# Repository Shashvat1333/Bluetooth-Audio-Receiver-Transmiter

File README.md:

# AUX-to-Bluetooth Audio Transmitter

A custom PCB I designed in KiCad that adds Bluetooth to anything with a headphone jack. Plug in an AUX cable, power it over USB-C, and stream to your wireless headphones.

## Table of Contents
- [Overview](#overview)
- [Repository Structure](#repository-structure)
- [Schematic & PCB](#schematic--pcb)
- [Firmware](#firmware)
- [Getting Started](#getting-started)
- [Ordering the Board](#ordering-the-board)
- [Bill of Materials (BOM)](#bill-of-materials-bom)
- [License](#license)

## Overview

Lots of good gear has no Bluetooth: an old TV, a record player, a treadmill, a car stereo with an AUX port. I wanted one small board that fixes that, so I designed it myself, from the schematic to the PCB layout.

### What it does

- **Wired to wireless:** Takes analog audio from a standard 3.5 mm AUX cable.
- **Clean conversion:** A 24-bit stereo ADC turns the sound into digital audio.
- **Bluetooth streaming:** An ESP32 sends the audio to your headphones or speaker.
- **Long range:** An RP-SMA connector lets you attach an external antenna.

### Real-world examples

- **Old TV:** Watch late at night with AirPods, no cable across the room.
- **Record player:** Listen to vinyl on wireless headphones.
- **Gym treadmill:** No cable in your way while you run.

---

## Repository Structure

```
Bluetooth-Audio-Receiver-Transmiter/
├── Hardware/    # KiCad project (schematic + PCB)
├── Gerbers/     # Files for the PCB factory
├── BOM/         # Full parts list
├── Firmware/    # ESP32 code
├── LICENSE.md
└── README.md
```

---

## Schematic & PCB

Audio goes in through the AUX jack, gets digitized, and is sent out over Bluetooth:

```
AUX jack → PCM1808 (ADC) → ESP32 (Bluetooth) → your headphones
```

| Part | What it does |
|---|---|
| ESP32-WROOM-32UE-N4 | The brain: Bluetooth pairing and streaming |
| PCM1808PWR | Turns analog sound into digital (I2S) audio |
| AP2112K-3.3 | Steps USB 5 V down to a steady 3.3 V |
| CH340C | USB-to-serial chip so you can upload code over USB-C |
| SJ-3523-SMT-TR | 3.5 mm stereo input jack |

---

## Firmware

The ESP32 needs code before the board will do anything. You upload it once with the Arduino IDE.

- **Code:** [firmware.ino](https://github.com/Shashvat1333/Bluetooth-Audio-Transmiter/blob/main/firmware.ino)
- **Board:** ESP32 Dev Module
- **Port:** USB-C (this one port both powers the board **and** uploads the code)

---

## Getting Started

1. **Download the firmware:** Grab the code from the [firmware.ino](https://github.com/Shashvat1333/Bluetooth-Audio-Transmiter/blob/main/firmware.ino).
2. **Set up the Arduino IDE:** Install the ESP32 board package (Boards Manager → search "esp32").
3. **Connect the board:** Plug the board into your computer with a USB-C cable. This one cable powers the board **and** uploads the code.
4. **Select the board:** Tools → Board → **ESP32 Dev Module**, then pick the correct port under Tools → Port.
5. **Upload:** Open the firmware file and click **Upload**.
6. **Plug in your audio:** Connect your audio source to the 3.5 mm AUX jack.
7. **Pair:** Put your headphones in pairing mode. The board connects automatically.

> **Tip:** If your computer doesn't show a port, install the CH340 USB driver and try a different USB-C cable (some are charge-only).

After the first upload, you only need USB-C power. Any phone charger works.

---

## Ordering the Board

Zip the `Gerbers` folder and upload it to your PCB maker (JLCPCB, PCBWay, etc.) with these settings:

| Setting | Value |
|---|---|
| Layers | [2] |
| Board size | [110 x 30 mm] |
| Thickness | [1.6 mm] |
| Copper | [1 oz] |
| Surface finish | [HASL lead-free] |
| Solder mask | [Green] |

---

## Bill of Materials (BOM)

| Part | What it's for | Qty | Unit | Total | Vendor |
| --- | --- | --- | --- | --- | --- |
| [UJ20-C-H-G-SMT-1-P16-TR](https://jlcpcb.com/partdetail/CUI-UJ20_C_H_G_SMT_1_P16TR/C45082766) | Use to power and program the esp32 | 1 | $0.86 | $0.86 | [JLCPCB](https://jlcpcb.com/partdetail/CUI-UJ20_C_H_G_SMT_1_P16TR/C45082766) |
| [Ceramic Capacitor Assortment Kit](https://www.aliexpress.com/item/1005012290380278.html?spm=a2g0o.productlist.main.2.328544d8SuTRhb&algo_pvid=40487480-af34-4fa0-991f-8491ed68449b&algo_exp_id=40487480-af34-4fa0-991f-8491ed68449b-1&pdp_ext_f=%7B%22order%22%3A%22786%22%2C%22eval%22%3A%221%22%2C%22fromPage%22%3A%22search%22%7D&pdp_npi=6%40dis%21CAD%2111.33%219.88%21%21%2152.17%2145.49%21%402103128817917564117867231e1157%2112000057969079635%21sea%21CA%218048449113%21X%211%210%21n_tag%3A-29911%3Bd%3A979b4513%3Bm03_new_user%3A-29895%3BpisId%3A5000000218598348&curPageLogUid=g6HIOIDwDsUK&utparam-url=scene%3Asearch%7Cquery_from%3A%7Cx_object_id%3A1005012290380278%7C_p_origin_prod%3A) | Ceramic capacitors are tiny passive electronic components used here to filter out electrical noise on power rails and block DC voltage while letting audio signals pass through. | 1 | $13.64 | $13.64 | [Aliexpress](https://www.aliexpress.com/item/1005012290380278.html?spm=a2g0o.productlist.main.2.328544d8SuTRhb&algo_pvid=40487480-af34-4fa0-991f-8491ed68449b&algo_exp_id=40487480-af34-4fa0-991f-8491ed68449b-1&pdp_ext_f=%7B%22order%22%3A%22786%22%2C%22eval%22%3A%221%22%2C%22fromPage%22%3A%22search%22%7D&pdp_npi=6%40dis%21CAD%2111.33%219.88%21%21%2152.17%2145.49%21%402103128817917564117867231e1157%2112000057969079635%21sea%21CA%218048449113%21X%211%210%21n_tag%3A-29911%3Bd%3A979b4513%3Bm03_new_user%3A-29895%3BpisId%3A5000000218598348&curPageLogUid=g6HIOIDwDsUK&utparam-url=scene%3Asearch%7Cquery_from%3A%7Cx_object_id%3A1005012290380278%7C_p_origin_prod%3A) |
| [AP2112K-3.3TRG1](https://jlcpcb.com/partdetail/DiodesIncorporated-AP2112K_33TRG1/C51118) | The AP2112K-3.3TRG1 is a low-dropout (LDO) voltage regulator used here to step down your incoming 5V power supply to a steady, clean 3.3V to power the ESP32 microcontroller and digital logic pins. | 1 | $0.19 | $0.19 | [JLCPCB](https://jlcpcb.com/partdetail/DiodesIncorporated-AP2112K_33TRG1/C51118) |
| [ESP32-WROOM-32UE-N4](https://jlcpcb.com/partdetail/EspressifSystems-ESP32_WROOM_32UEN4/C701344) | The ESP32 is a microcontroller used here to run firmware that receives the digital I2S audio stream from the PCM1808 and handles Wi-Fi or Bluetooth connectivity. | 1 | $4.50 | $4.50 | [JLCPCB](https://jlcpcb.com/partdetail/EspressifSystems-ESP32_WROOM_32UEN4/C701344) |
| [CH340C](https://www.aliexpress.com/item/1005007206307679.html?spm=a2g0o.productlist.main.2.14735d38jJiEP4&algo_pvid=08c2775b-a139-455d-8b44-be4d4204f0a8&algo_exp_id=08c2775b-a139-455d-8b44-be4d4204f0a8-1&pdp_ext_f=%7B%22order%22%3A%2220%22%2C%22eval%22%3A%221%22%2C%22fromPage%22%3A%22search%22%7D&pdp_npi=6%40dis%21CAD%214.39%214.39%21%21%213.02%213.02%21%402101c28d17917628228577887e0c6e%2112000039805627300%21sea%21CA%218048449113%21X%211%210%21n_tag%3A-29911%3Bd%3A979b4513%3Bm03_new_user%3A-29895&curPageLogUid=tDRd9NJte0Jp&utparam-url=scene%3Asearch%7Cquery_from%3A%7Cx_object_id%3A1005007206307679%7C_p_origin_prod%3A) | The CH340C is a USB-to-UART bridge IC used here to let your computer communicate with the ESP32 for programming and debugging via a standard USB-C cable. | 1 | $4.20 | $4.20 | [Aliexpress](https://www.aliexpress.com/item/1005007206307679.html?spm=a2g0o.productlist.main.2.14735d38jJiEP4&algo_pvid=08c2775b-a139-455d-8b44-be4d4204f0a8&algo_exp_id=08c2775b-a139-455d-8b44-be4d4204f0a8-1&pdp_ext_f=%7B%22order%22%3A%2220%22%2C%22eval%22%3A%221%22%2C%22fromPage%22%3A%22search%22%7D&pdp_npi=6%40dis%21CAD%214.39%214.39%21%21%213.02%213.02%21%402101c28d17917628228577887e0c6e%2112000039805627300%21sea%21CA%218048449113%21X%211%210%21n_tag%3A-29911%3Bd%3A979b4513%3Bm03_new_user%3A-29895&curPageLogUid=tDRd9NJte0Jp&utparam-url=scene%3Asearch%7Cquery_from%3A%7Cx_object_id%3A1005007206307679%7C_p_origin_prod%3A) |
| [[NC]2.4GHz 3dBi WiFi 2.4g Antenna +15cm Aerial RP-SMA Male Wireless Router PCI U.FL IPX To RP SMA Male Pigtail Cable[NC]](https://www.aliexpress.com/item/1005012839987115.html?spm=a2g0o.productlist.main.17.22487e4aAc5l2Y&algo_pvid=5c910e90-451d-4eb2-b6c2-a9b67833a777&algo_exp_id=5c910e90-451d-4eb2-b6c2-a9b67833a777-16&pdp_ext_f=%7B%22order%22%3A%228%22%2C%22eval%22%3A%221%22%2C%22fromPage%22%3A%22search%22%7D&pdp_npi=6%40dis%21CAD%2112.90%215.00%21%21%2159.41%2123.03%21%402101e80b17915677645397405e0de8%2112000059523438374%21sea%21CA%218048449113%21X%211%210%21n_tag%3A-29911%3Bd%3A979b4513%3Bm03_new_user%3A-29895%3BpisId%3A5000000216666461&curPageLogUid=c4JAZG0wstCM&utparam-url=scene%3Asearch%7Cquery_from%3A%7Cx_object_id%3A1005012839987115%7C_p_origin_prod%3A) | That antenna and pigtail cable are used here to connect an external 2.4GHz antenna to the ESP32 module's IPEX connector for reliable Wi-Fi and Bluetooth signal reception. | 1 | $10.23 | $10.23 | [Aliexpress](https://www.aliexpress.com/item/1005012839987115.html?spm=a2g0o.productlist.main.17.22487e4aAc5l2Y&algo_pvid=5c910e90-451d-4eb2-b6c2-a9b67833a777&algo_exp_id=5c910e90-451d-4eb2-b6c2-a9b67833a777-16&pdp_ext_f=%7B%22order%22%3A%228%22%2C%22eval%22%3A%221%22%2C%22fromPage%22%3A%22search%22%7D&pdp_npi=6%40dis%21CAD%2112.90%215.00%21%21%2159.41%2123.03%21%402101e80b17915677645397405e0de8%2112000059523438374%21sea%21CA%218048449113%21X%211%210%21n_tag%3A-29911%3Bd%3A979b4513%3Bm03_new_user%3A-29895%3BpisId%3A5000000216666461&curPageLogUid=c4JAZG0wstCM&utparam-url=scene%3Asearch%7Cquery_from%3A%7Cx_object_id%3A1005012839987115%7C_p_origin_prod%3A) |
| [Mini Optical Audio Adapter 3.5mm Female Jack to Digital Toslink Male Plug For Amplifier Optical Audio Cable](https://www.aliexpress.com/item/1005009093776595.html?spm=a2g0o.productlist.main.6.18e47348zV59Cg&algo_pvid=f7d36bc0-4bf3-4565-acc6-9d3dda11366b&algo_exp_id=f7d36bc0-4bf3-4565-acc6-9d3dda11366b-5&pdp_ext_f=%7B%22order%22%3A%22344%22%2C%22eval%22%3A%221%22%2C%22fromPage%22%3A%22search%22%7D&pdp_npi=6%40dis%21CAD%213.75%213.75%21%21%2117.28%2117.28%21%402101de2517917626141065991e144b%2112000047887714520%21sea%21CA%218048449113%21X%211%210%21n_tag%3A-29911%3Bd%3A979b4513%3Bm03_new_user%3A-29895&curPageLogUid=tx4CSSuvm17a&utparam-url=scene%3Asearch%7Cquery_from%3A%7Cx_object_id%3A1005009093776595%7C_p_origin_prod%3A) | That adapter is used to convert a standard 3.5mm audio cable connection into a digital optical Toslink plug. | 1 | $2.97 | $2.97 | [Aliexpress](https://www.aliexpress.com/item/1005009093776595.html?spm=a2g0o.productlist.main.6.18e47348zV59Cg&algo_pvid=f7d36bc0-4bf3-4565-acc6-9d3dda11366b&algo_exp_id=f7d36bc0-4bf3-4565-acc6-9d3dda11366b-5&pdp_ext_f=%7B%22order%22%3A%22344%22%2C%22eval%22%3A%221%22%2C%22fromPage%22%3A%22search%22%7D&pdp_npi=6%40dis%21CAD%213.75%213.75%21%21%2117.28%2117.28%21%402101de2517917626141065991e144b%2112000047887714520%21sea%21CA%218048449113%21X%211%210%21n_tag%3A-29911%3Bd%3A979b4513%3Bm03_new_user%3A-29895&curPageLogUid=tx4CSSuvm17a&utparam-url=scene%3Asearch%7Cquery_from%3A%7Cx_object_id%3A1005009093776595%7C_p_origin_prod%3A) |
| [SJ-3523-SMT-TR](https://jlcpcb.com/partdetail/CUI-SJ_3523_SMTTR/C4991872) | The SJ-3523-SMT-TR is a surface-mount 3.5mm stereo audio jack used here to plug in your audio cable and bring the analog sound signals onto the PCB. | 1 | $1.42 | $1.42 | [JLCPCB](https://jlcpcb.com/partdetail/CUI-SJ_3523_SMTTR/C4991872) |
| [PCM1808PWR](https://jlcpcb.com/partdetail/TexasInstruments-PCM1808PWR/C55513) | The PCM1808PWR is a 24-bit stereo analog-to-digital converter (ADC) used here to convert your analog audio signals into digital I2S data for the ESP32. | 1 | $0.79 | $0.79 | [JLCPCB](https://jlcpcb.com/partdetail/TexasInstruments-PCM1808PWR/C55513) |
| [BC817](https://jlcpcb.com/partdetail/2494-BC817_RANGE_100_250/C2137) | The BC817 is a general-purpose NPN transistor used here to act as a switch—typically for driving indicator LEDs, controlling power lines, or handling USB reset signals in your circuit. | 2 | $0.07 | $0.14 | [JLCPCB](https://jlcpcb.com/partdetail/2494-BC817_RANGE_100_250/C2137) |
| [Resistor Kit](https://www.aliexpress.com/item/1005011772534173.html?spm=a2g0o.productlist.main.1.32f07cfcDAKt5h&algo_pvid=bd1a798f-1e1b-462e-8c2c-269d4ca4ad23&algo_exp_id=bd1a798f-1e1b-462e-8c2c-269d4ca4ad23-0&pdp_ext_f=%7B%22order%22%3A%229084%22%2C%22spu_best_type%22%3A%22price%22%2C%22eval%22%3A%221%22%2C%22fromPage%22%3A%22search%22%7D&pdp_npi=6%40dis%21CAD%216.03%214.58%21%21%2127.77%2121.09%21%402101e7a317917668551207826e0eb3%2112000056500803485%21sea%21CA%218048449113%21X%211%210%21n_tag%3A-29911%3Bd%3A979b4513%3Bm03_new_user%3A-29895%3BpisId%3A5000000218598348&curPageLogUid=XejYrzptMOfz&utparam-url=scene%3Asearch%7Cquery_from%3A%7Cx_object_id%3A1005011772534173%7C_p_origin_prod%3A) | A resistor kit is a collection of various resistors with different resistance values used across your circuit for setting up pull-up/pull-down lines, limiting current to LEDs, and biasing transistors. | 1 | $4.78 | $4.78 | [Aliexpress](https://www.aliexpress.com/item/1005011772534173.html?spm=a2g0o.productlist.main.1.32f07cfcDAKt5h&algo_pvid=bd1a798f-1e1b-462e-8c2c-269d4ca4ad23&algo_exp_id=bd1a798f-1e1b-462e-8c2c-269d4ca4ad23-0&pdp_ext_f=%7B%22order%22%3A%229084%22%2C%22spu_best_type%22%3A%22price%22%2C%22eval%22%3A%221%22%2C%22fromPage%22%3A%22search%22%7D&pdp_npi=6%40dis%21CAD%216.03%214.58%21%21%2127.77%2121.09%21%402101e7a317917668551207826e0eb3%2112000056500803485%21sea%21CA%218048449113%21X%211%210%21n_tag%3A-29911%3Bd%3A979b4513%3Bm03_new_user%3A-29895%3BpisId%3A5000000218598348&curPageLogUid=XejYrzptMOfz&utparam-url=scene%3Asearch%7Cquery_from%3A%7Cx_object_id%3A1005011772534173%7C_p_origin_prod%3A) |
| [PCB Manufacturing](https://cart.jlcpcb.com/quote?stencilLayer=2&stencilWidth=100&stencilLength=100&stencilCounts=5&plateType=1&spm=Jlcpcb.Homepage.1010) | This will be the board where I will connect all my parts too | 1 | $8.53 | $8.53 | [JLCPCB](https://cart.jlcpcb.com/quote?stencilLayer=2&stencilWidth=100&stencilLength=100&stencilCounts=5&plateType=1&spm=Jlcpcb.Homepage.1010) |
| **Parts subtotal** | — | — | — | **$52.25** | — |
| **Tax & shipping** | — | — | — | **$12.00** | — |
| **Total** | — | — | — | **$64.25** | — |

---

## License

[License, e.g. CERN-OHL-P or MIT]. See [LICENSE.md](https://github.com/Shashvat1333/Bluetooth-Audio-Transmiter/blob/main/LICENCE.md).

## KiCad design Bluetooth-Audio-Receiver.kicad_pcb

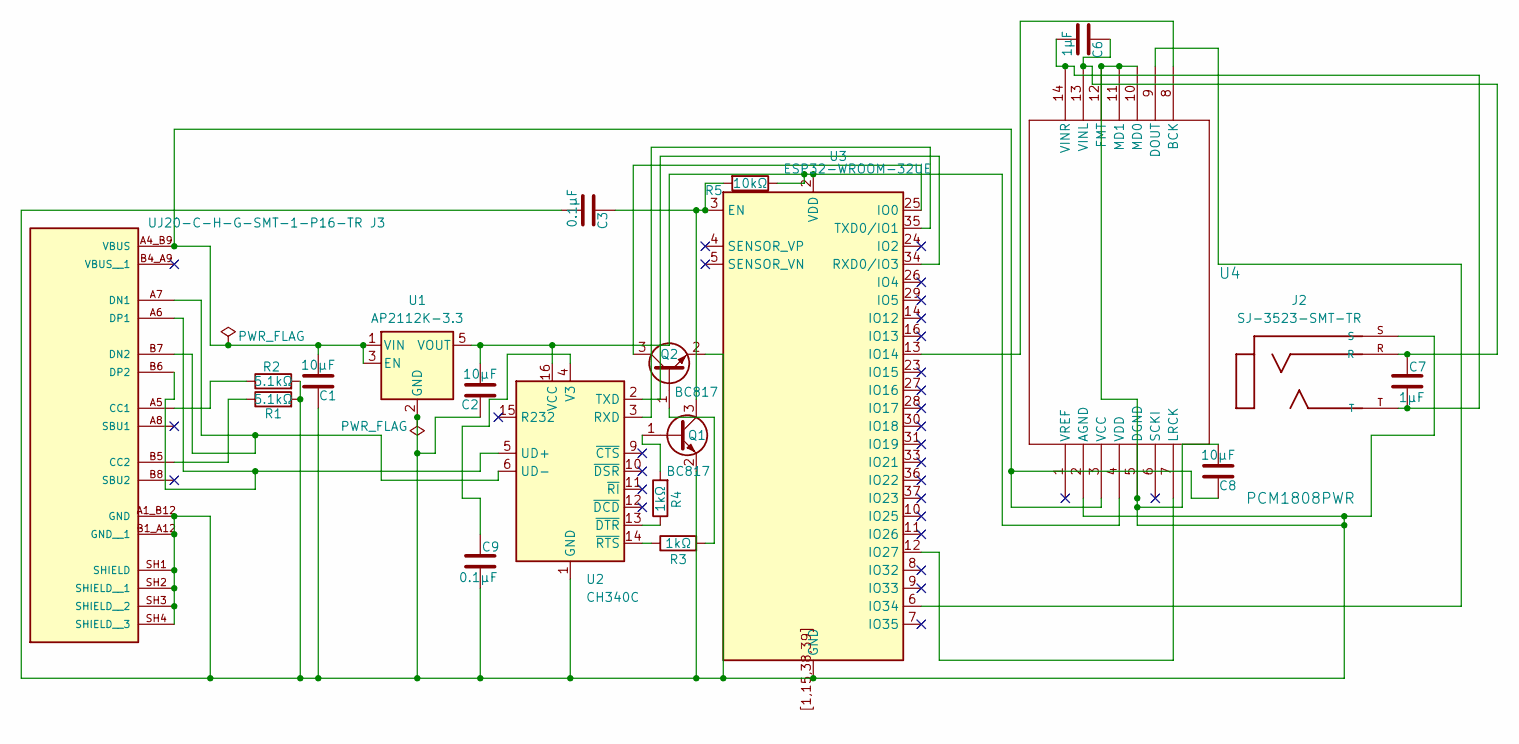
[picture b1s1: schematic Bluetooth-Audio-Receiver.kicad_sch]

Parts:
C1, C2, C8: 10μF; C_Disc_D5.0mm_W2.5mm_P5.00mm
C3, C9: 0.1μF; C_Disc_D5.0mm_W2.5mm_P5.00mm
C6, C7: 1μF; C_Disc_D5.0mm_W2.5mm_P5.00mm
J2: SJ-3523-SMT-TR; Jack_3.5mm_CUI_SJ-3523-SMT_Horizontal
J3: UJ20-C-H-G-SMT-1-P16-TR; SAMESKY_UJ20-C-H-G-SMT-1-P16-TR; PARTREV 1.0
Q1, Q2: BC817; SOT-23
R1, R2: 5.1kΩ; R_Axial_DIN0207_L6.3mm_D2.5mm_P10.16mm_Horizontal
R3, R4: 1kΩ; R_Axial_DIN0207_L6.3mm_D2.5mm_P10.16mm_Horizontal
R5: 10kΩ; R_Axial_DIN0207_L6.3mm_D2.5mm_P10.16mm_Horizontal
U1: AP2112K-3.3; SOT-23-5
U2: CH340C; SOIC-16_3.9x9.9mm_P1.27mm
U3: ESP32-WROOM-32UE
U4: PCM1808PWR; TSSOP-14_4.4x5mm_P0.65mm

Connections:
unnamed: J3.A5 (CC1), R2.1
unnamed: J3.B5 (CC2), R1.1
unnamed: J3.A7 (DN1), J3.B7 (DN2), U2.6 (UD-)
unnamed: J3.A6 (DP1), J3.B6 (DP2), U2.5 (UD+)
unnamed: C1.2, C2.2, C3.1, C8.1, C9.1, J2.S, J3.A1_B12 (GND), J3.B1_A12 (GND__1), J3.SH1 (SHIELD), J3.SH2 (SHIELD__1), J3.SH3 (SHIELD__2), J3.SH4 (SHIELD__3), Q1.2 (E), Q2.2 (E), R1.2, R2.2, U1.2 (GND), U2.1 (GND), U3.1 (GND), U3.15 (GND), U3.38 (GND), U3.39 (GND), U3.[1,15,38,39] (GND), U4.2 (AGND), U4.5 (DGND), U4.10 (MD0), U4.11 (MD1), U4.12 (FMT)
unnamed: C1.1, C8.2, J3.A4_B9 (VBUS), U1.1 (VIN), U1.3 (EN), U4.3 (VCC)
unnamed: Q1.1 (B), R4.2
unnamed: C3.2, Q1.3 (C), R5.2, U3.3 (EN)
unnamed: Q2.1 (B), R3.2
unnamed: Q2.3 (C), U3.25 (IO0)
unnamed: C2.1, R5.1, U1.5 (VOUT), U2.16 (VCC), U3.2 (VDD), U4.4 (VDD)
unnamed: U2.3 (RXD), U3.35 (TXD0/IO1)
unnamed: U2.2 (TXD), U3.34 (RXD0/IO3)
unnamed: C9.2, U2.4 (V3)
unnamed: R4.1, U2.13 (~DTR)
unnamed: R3.1, U2.14 (~RTS)
unnamed: U3.13 (IO14), U4.8 (BCK)
unnamed: U3.12 (IO27), U4.7 (LRCK)
unnamed: U3.6 (IO34), U4.9 (DOUT)
unnamed: C6.2, C7.2, J2.R, U4.13 (VINL)
unnamed: C6.1, C7.1, J2.T, U4.14 (VINR)

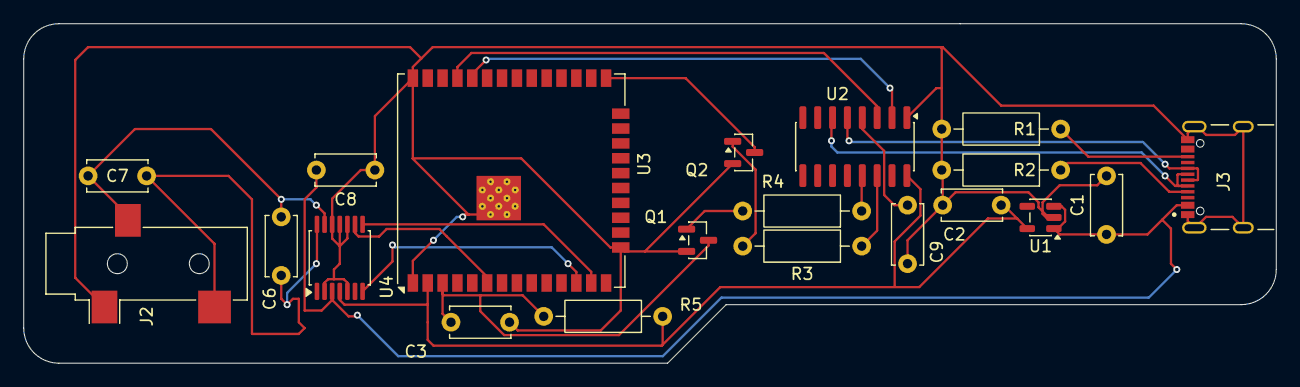
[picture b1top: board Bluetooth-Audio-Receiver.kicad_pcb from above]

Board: 2 copper layers, 107.0 x 29.0 mm, 20 parts (0 on the bottom side), 21 nets.

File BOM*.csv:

Part,What it's for,Qty,Unit (USD),Total (USD),Vendor,Link
UJ20-C-H-G-SMT-1-P16-TR,Use to power and program the esp32,1,0.86,0.86,JLCPCB,https://jlcpcb.com/partdetail/CUI-UJ20_C_H_G_SMT_1_P16TR/C45082766
Ceramic Capacitor Assortment Kit,"Ceramic capacitors are tiny passive electronic components used here to filter out electrical noise on power rails and block DC voltage while letting audio signals pass through.",1,13.64,13.64,Aliexpress,https://www.aliexpress.com/item/1005012290380278.html
AP2112K-3.3TRG1,"The AP2112K-3.3TRG1 is a low-dropout (LDO) voltage regulator used here to step down your incoming 5V power supply to a steady, clean 3.3V to power the ESP32 microcontroller and digital logic pins.",1,0.19,0.19,JLCPCB,https://jlcpcb.com/partdetail/DiodesIncorporated-AP2112K_33T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
ESP32-WROOM-32UE-N4,"The ESP32 is a microcontroller used here to run firmware that receives the digital I2S audio stream from the PCM1808 and handles Wi-Fi or Bluetooth connectivity.",1,4.50,4.50,JLCPCB,https://jlcpcb.com/partdetail/EspressifSystems-ESP32_WROOM_3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
CH340C,"The CH340C is a USB-to-UART bridge IC used here to let your computer communicate with the ESP32 for programming and debugging via a standard USB-C cable.",1,4.20,4.20,Aliexpress,https://www.aliexpress.com/item/1005007206307679.html
[NC]2.4GHz 3dBi WiFi 2.4g Antenna +15cm Aerial RP-SMA Male Wireless Router PCI U.FL IPX To RP SMA Male Pigtail Cable[NC],"That antenna and pigtail cable are used here to connect an external 2.4GHz antenna to the ESP32 module's IPEX connector for reliable Wi-Fi and Bluetooth signal reception.",1,10.23,10.23,Aliexpress,https://www.aliexpress.com/item/1005012839987115.html
Mini Optical Audio Adapter 3.5mm Female Jack to Digital Toslink Male Plug For Amplifier Optical Audio Cable,"That adapter is used to convert a standard 3.5mm audio cable connection into a digital optical Toslink plug.",1,2.97,2.97,Aliexpress,https://www.aliexpress.com/item/1005009093776595.html
SJ-3523-SMT-TR,"The SJ-3523-SMT-TR is a surface-mount 3.5mm stereo audio jack used here to plug in your audio cable and bring the analog sound signals onto the PCB.",1,1.42,1.42,JLCPCB,https://jlcpcb.com/partdetail/CUI-SJ_3523_SMTTR/C4991872
PCM1808PWR,"The PCM1808PWR is a 24-bit stereo analog-to-digital converter (ADC) used here to convert your analog audio signals into digital I2S data for the ESP32.",1,0.79,0.79,JLCPCB,https://jlcpcb.com/partdetail/TexasInstruments-PCM1808PWR/C55513
BC817,"The BC817 is a general-purpose NPN transistor used here to act as a switch—typically for driving indicator LEDs, controlling power lines, or handling USB reset signals in your circuit.",2,0.07,0.14,JLCPCB,https://jlcpcb.com/partdetail/2494-BC817_RANGE_100_250/C2137
Resistor Kit,"A resistor kit is a collection of various resistors with different resistance values used across your circuit for setting up pull-up/pull-down lines, limiting current to LEDs, and biasing transistors.",1,4.78,4.78,Aliexpress,https://www.aliexpress.com/item/1005011772534173.html
PCB Manufacturing,This will be the board where I will connect all my parts too,1,8.53,8.53,JLCPCB,
Parts subtotal,,,,52.25,,
Tax & shipping,for the whole order,,,12.00,,
Total,,,,64.25,,
